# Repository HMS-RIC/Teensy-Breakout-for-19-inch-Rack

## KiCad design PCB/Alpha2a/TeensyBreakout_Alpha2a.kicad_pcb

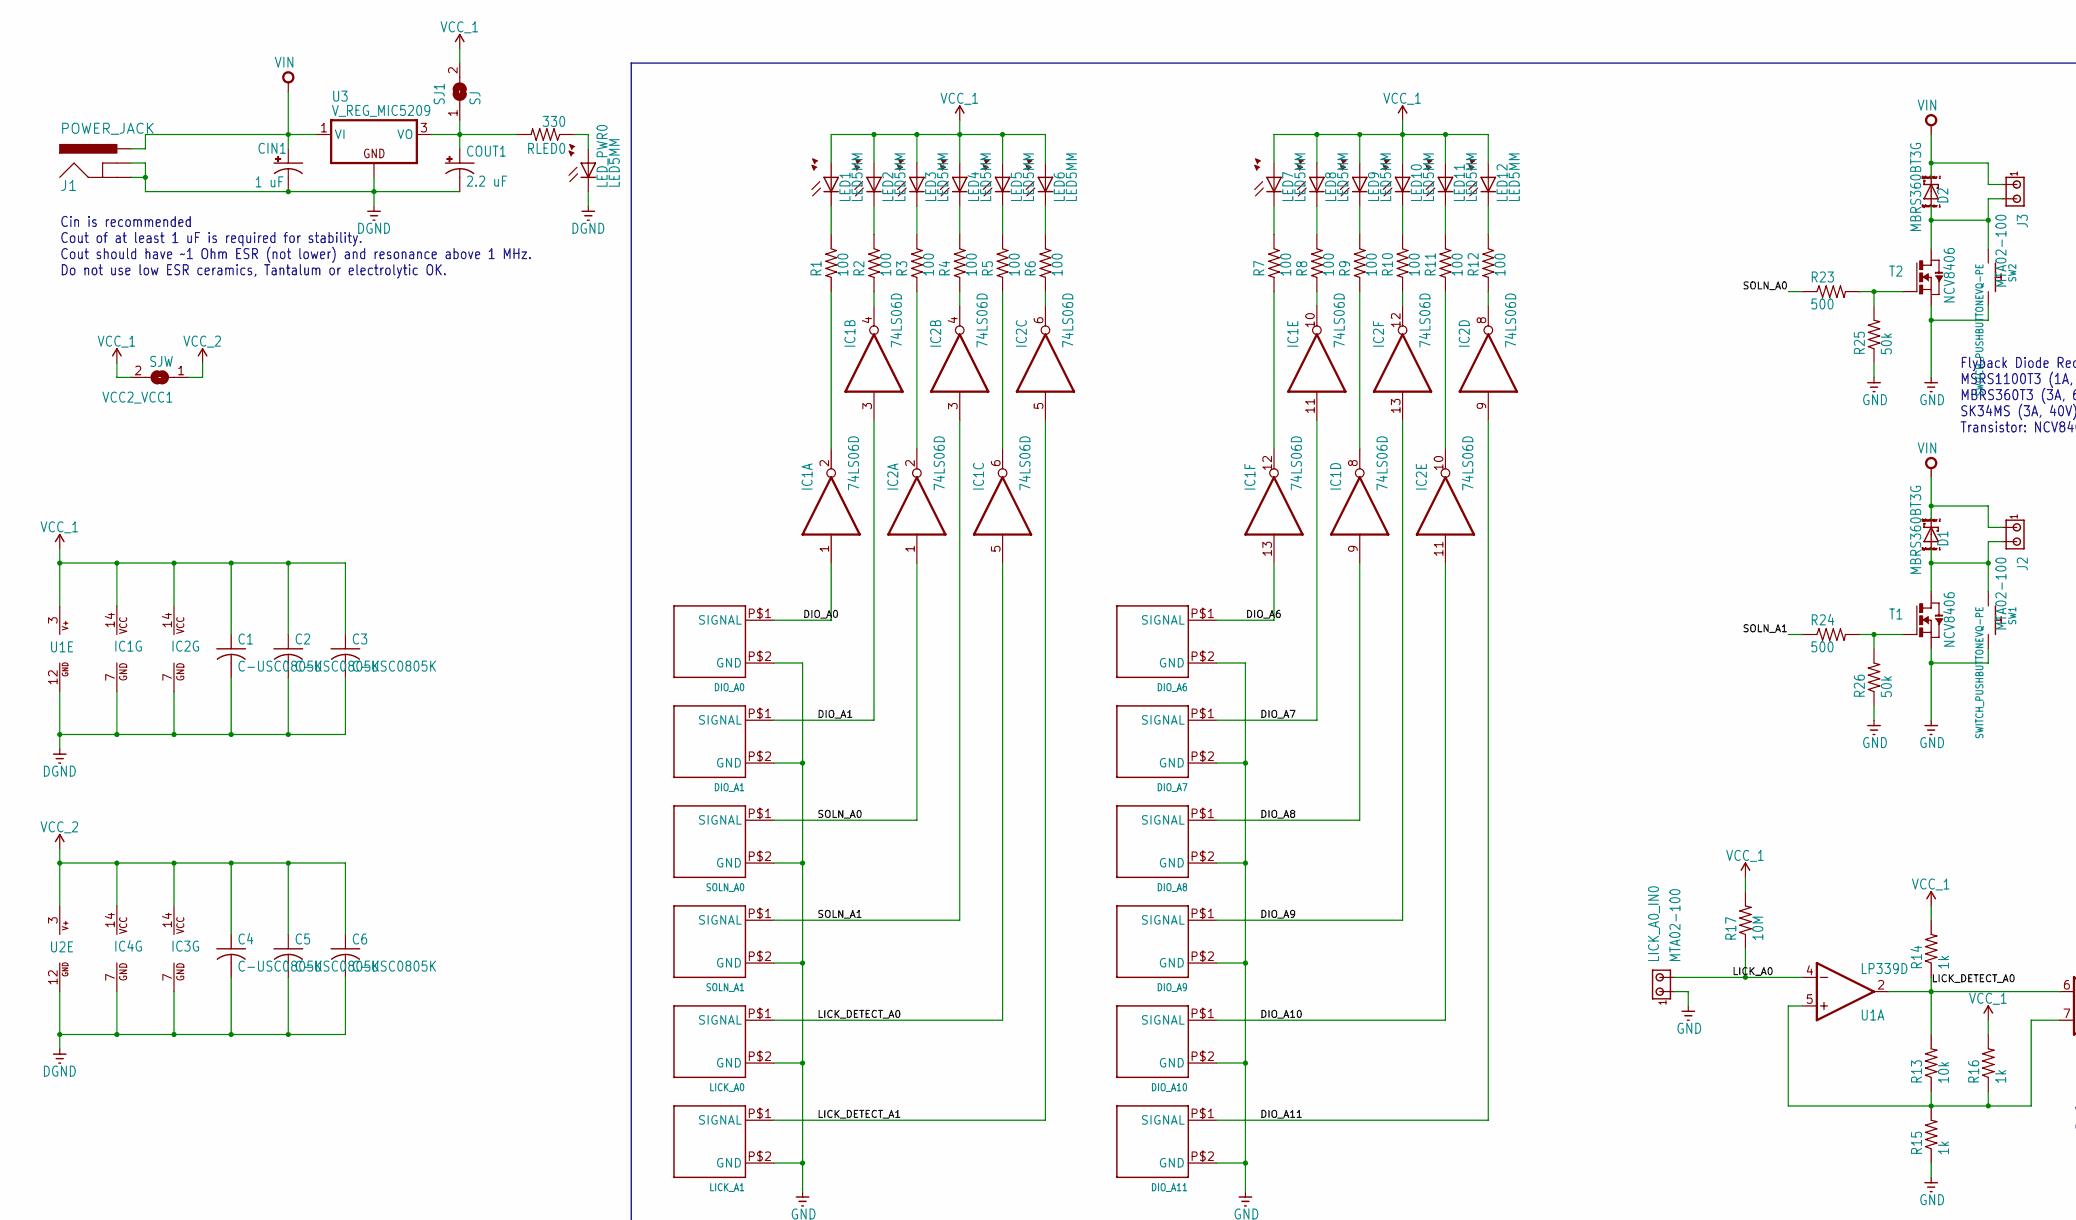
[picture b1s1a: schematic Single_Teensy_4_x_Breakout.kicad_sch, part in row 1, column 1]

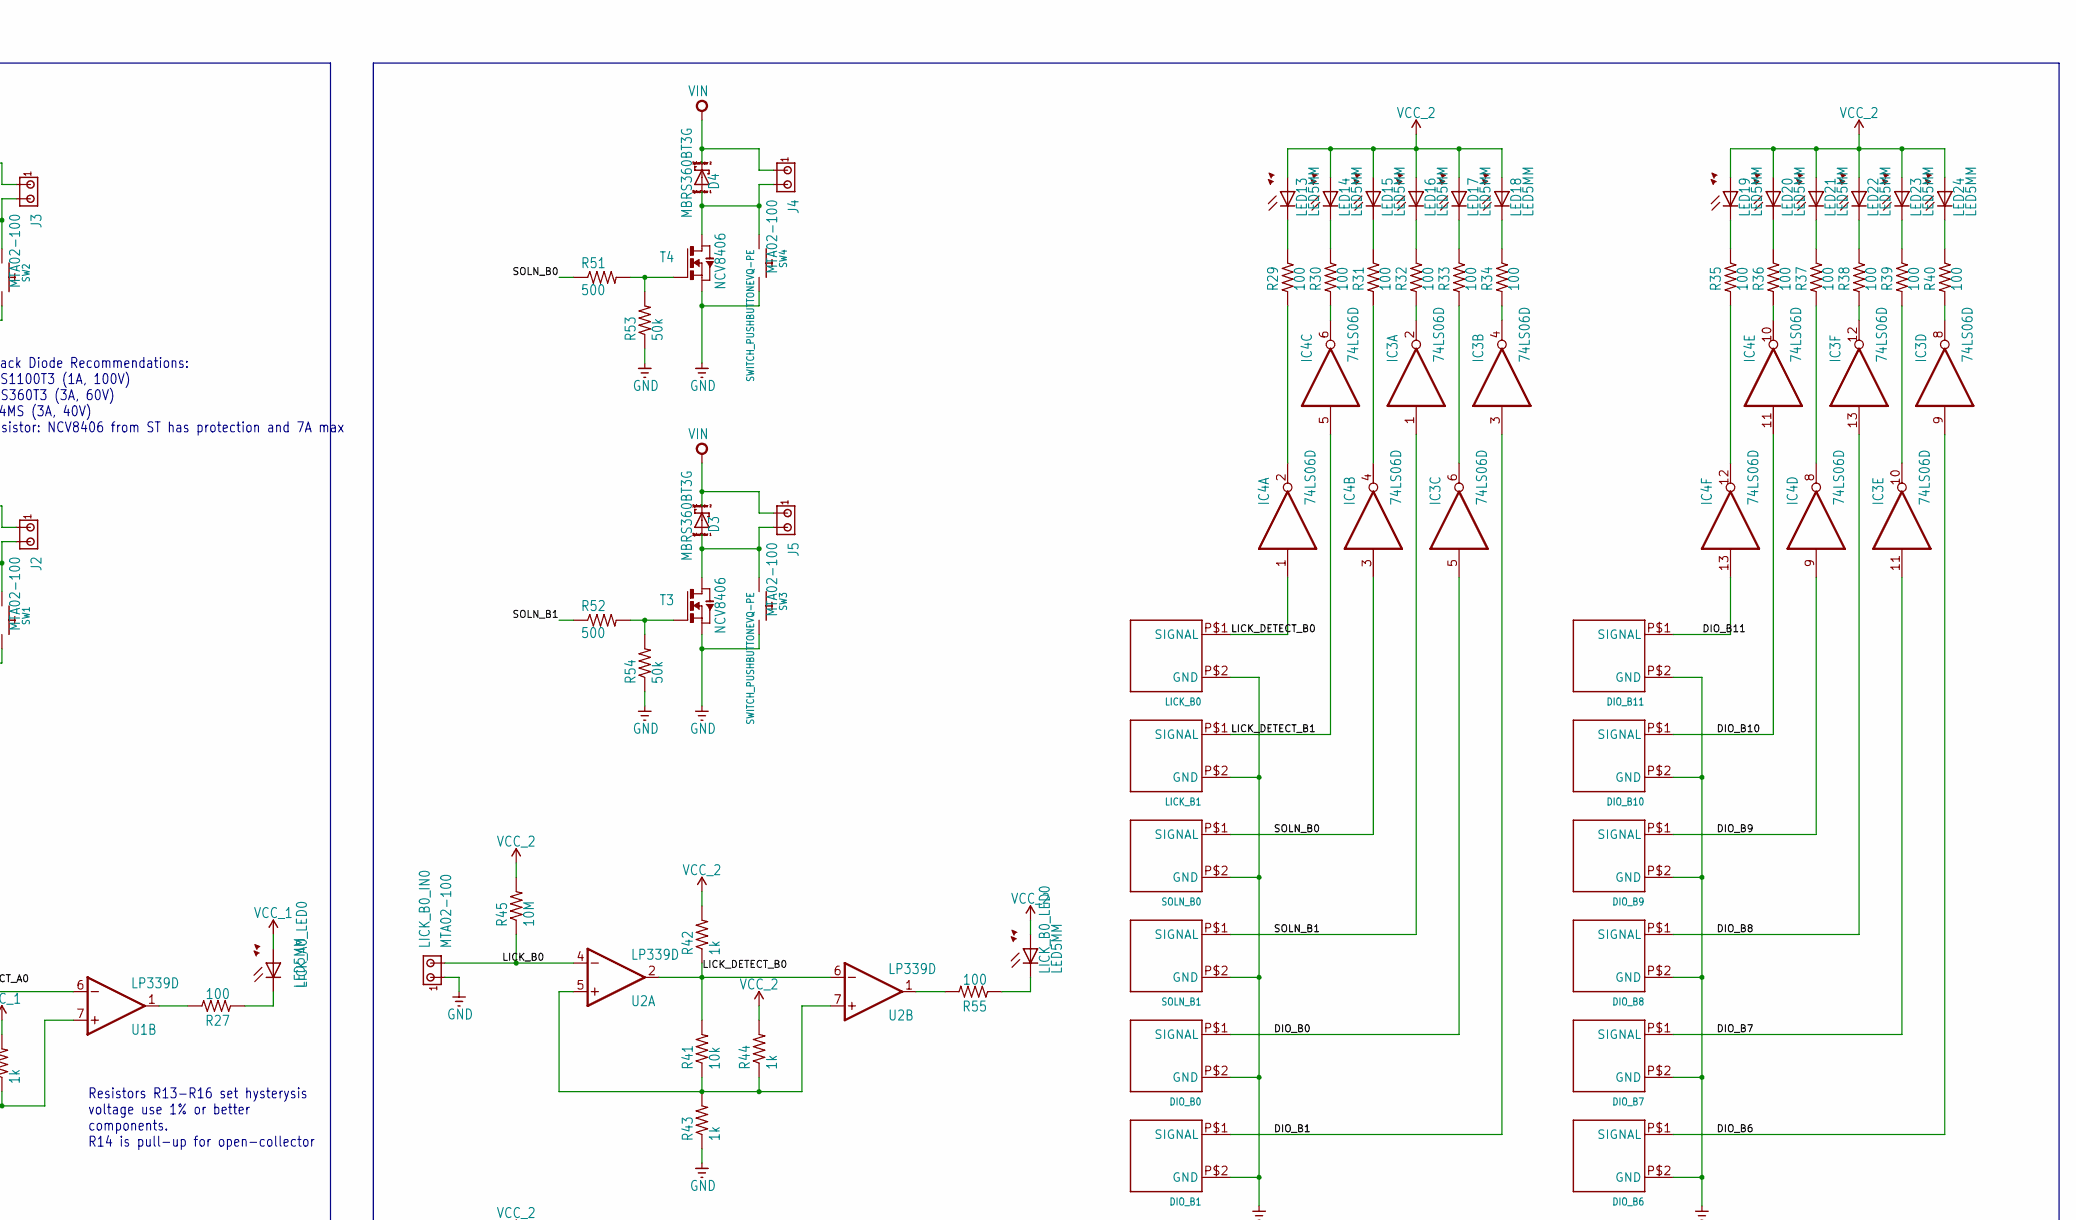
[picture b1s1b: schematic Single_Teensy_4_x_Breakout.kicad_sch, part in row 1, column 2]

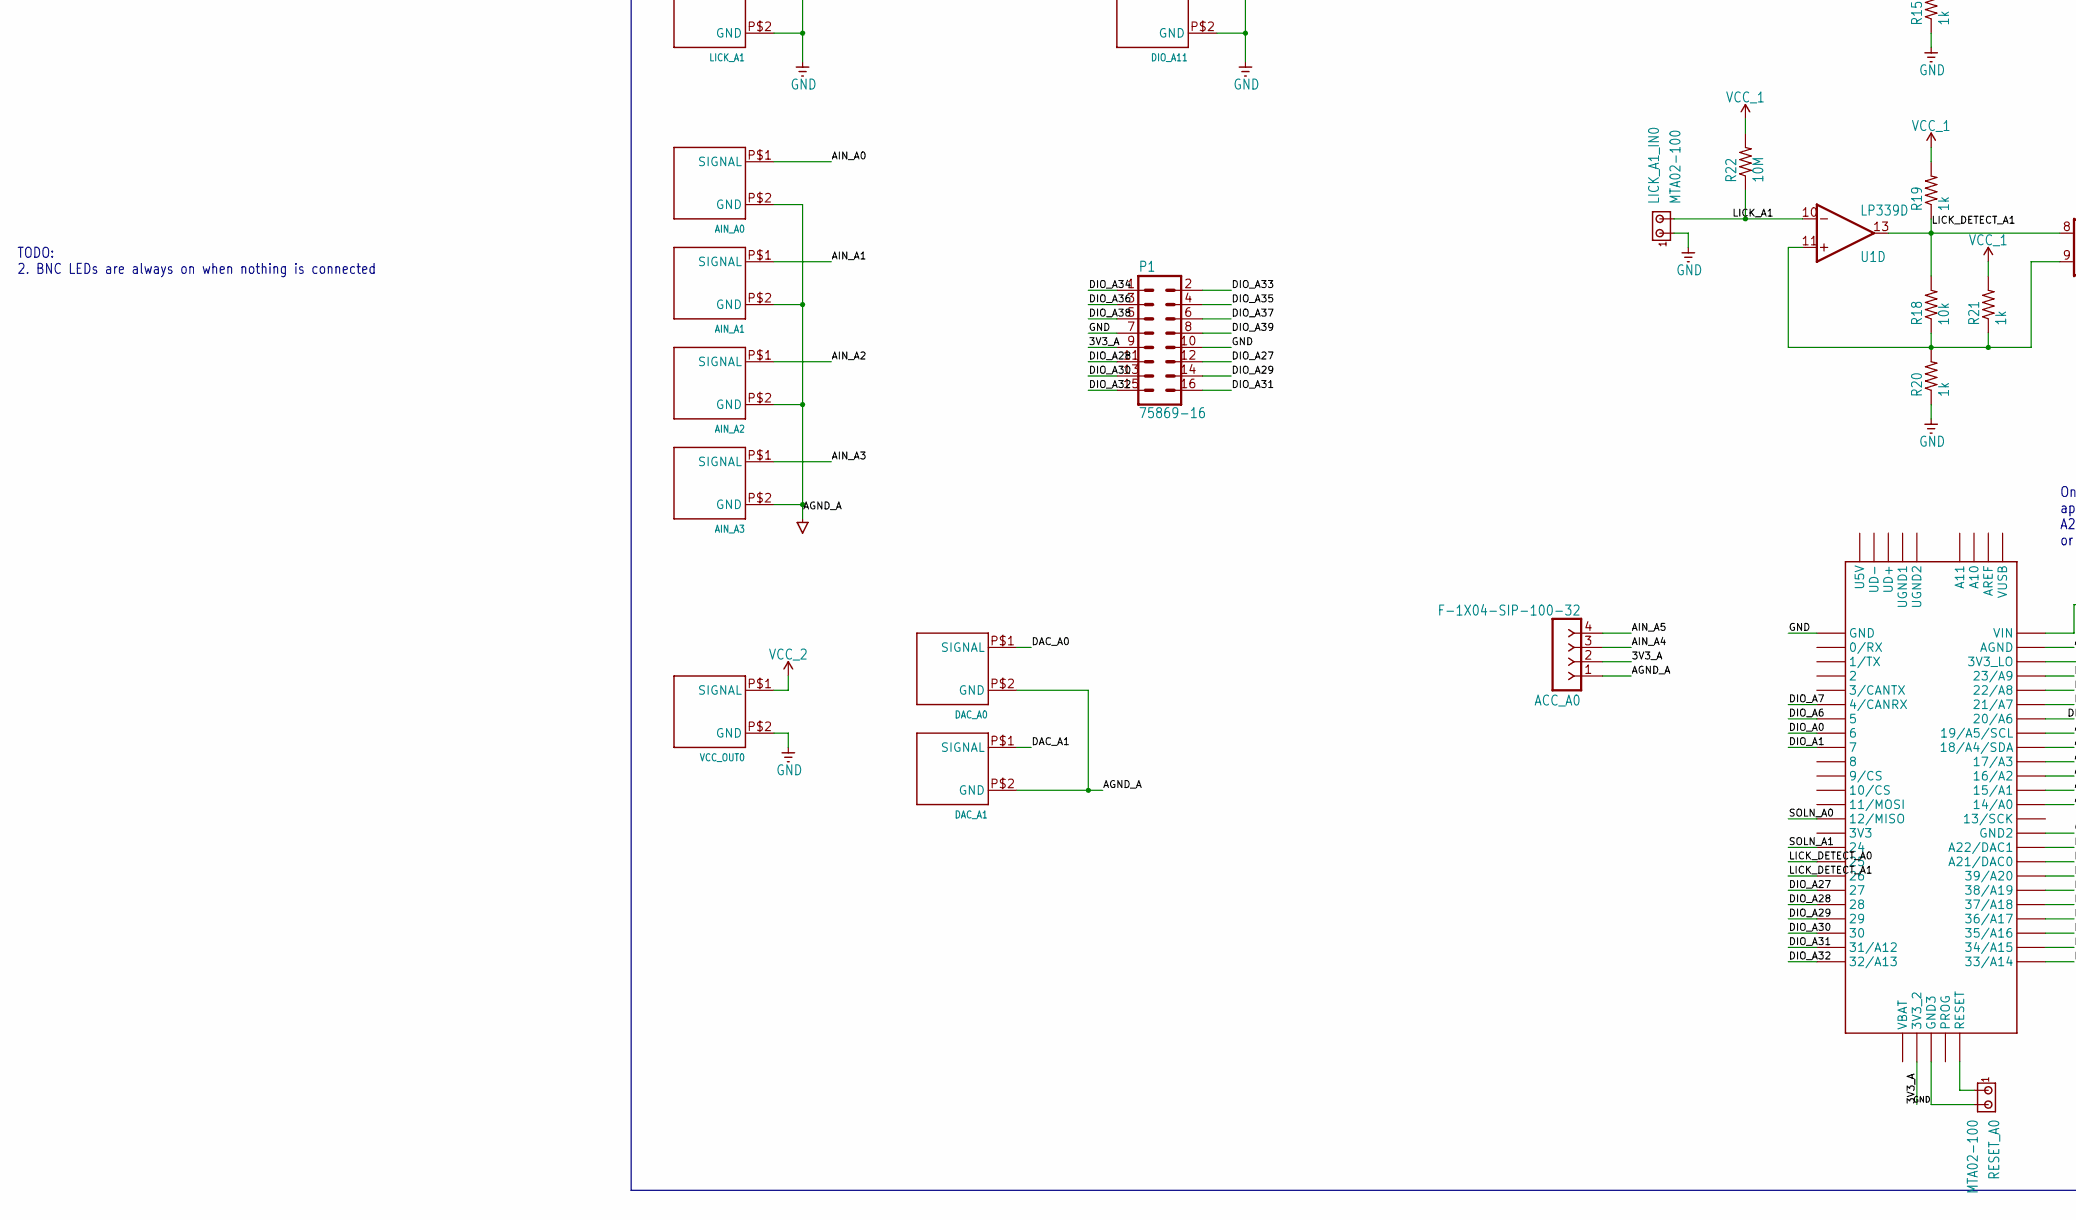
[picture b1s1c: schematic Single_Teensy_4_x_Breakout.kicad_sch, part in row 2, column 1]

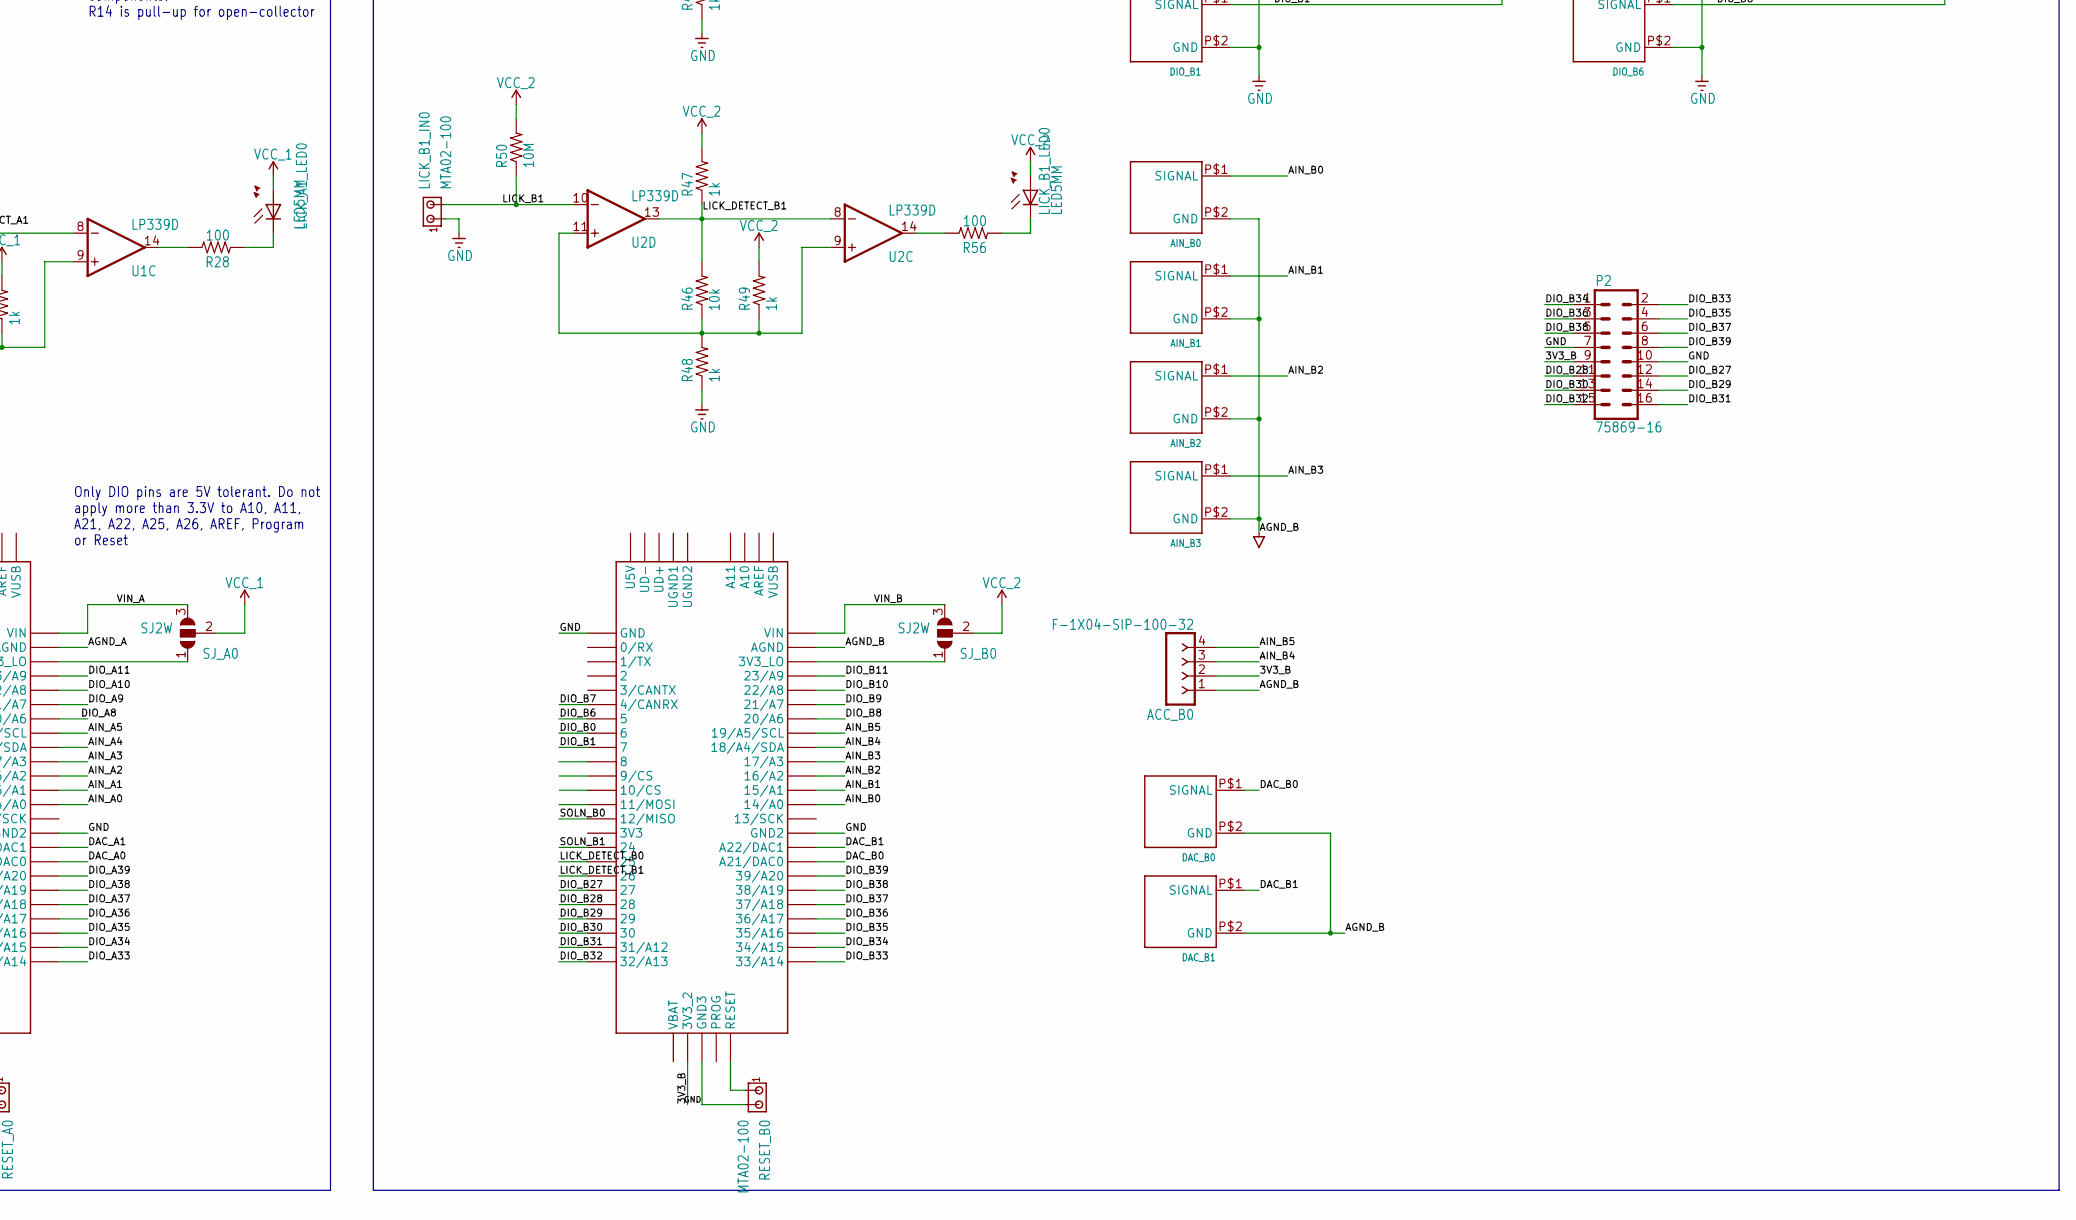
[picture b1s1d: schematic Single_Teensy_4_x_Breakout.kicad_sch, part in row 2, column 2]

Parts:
ACC_A0: F-1X04-SIP-100-32; SIP-100-04-32
ACC_B0: F-1X04-SIP-100-32; SIP-100-04-32
AIN_A0, AIN_A1, AIN_A2, AIN_A3: BNC_VERTICAL
AIN_B0, AIN_B1, AIN_B2, AIN_B3: BNC_VERTICAL
C1, C2, C3, C4, C5, C6: C-USC0805K; C0805K
CIN1: 1 uF; E2,5-5
COUT1: 2.2 uF; E2,5-5
D1, D2, D3, D4: MBRS360BT3G; DIODE_SMB
DAC_A0, DAC_A1: BNC_VERTICAL
DAC_B0, DAC_B1: BNC_VERTICAL
DIO_A0, DIO_A1, DIO_A6, DIO_A7, DIO_A8, DIO_A9, DIO_A10, DIO_A11: BNC_VERTICAL
DIO_B0, DIO_B1, DIO_B6, DIO_B7, DIO_B8, DIO_B9, DIO_B10, DIO_B11: BNC_VERTICAL
IC1, IC2, IC3, IC4: 74LS06D; SO14
J1: POWER_JACK; POWER_JACK_PTH
J2, J3, J4, J5: MTA02-100; 10X02MTA
LED1, LED2, LED3, LED4, LED5, LED6, LED7, LED8, LED9, LED10, LED11, LED12, LED13, LED14, LED15, LED16, LED17, LED18, LED19, LED20, LED21, LED22, LED23, LED24: LED5MM
LED_PWR0: LED5MM
LICK_A0, LICK_A1: BNC_VERTICAL
LICK_A0_IN0, LICK_A1_IN0: MTA02-100; 10X02MTA
LICK_A0_LED0, LICK_A1_LED0: LED5MM
LICK_B0, LICK_B1: BNC_VERTICAL
LICK_B0_IN0, LICK_B1_IN0: MTA02-100; 10X02MTA
LICK_B0_LED0, LICK_B1_LED0: LED5MM
P1, P2: 75869-16
R1, R2, R3, R4, R5, R6, R7, R8, R9, R10, R11, R12, R29, R30, R31, R32, R33, R34, R35, R36, R37, R38, R39, R40: 100; R1206MP
R13, R18, R41, R46: 10k; M0805
R14, R15, R16, R19, R20, R21, R42, R43, R44, R47, R48, R49: 1k; M0805
R17, R22, R45, R50: 10M; M0805
R23, R24, R51, R52: 500; M1206
R25, R26, R53, R54: 50k; M1206
R27, R28, R55, R56: 100; R1206
RESET_A0: MTA02-100; 10X02MTA
RESET_B0: MTA02-100; 10X02MTA
RLED0: 330; R0805
SJ1: SJ
SJ_A0: SJ2W; SJ_2
SJ_B0: SJ2W; SJ_2
SOLN_A0, SOLN_A1: BNC_VERTICAL
SOLN_B0, SOLN_B1: BNC_VERTICAL
SW1, SW2, SW3, SW4: SWITCH_PUSHBUTTONEVQ-PE; TACT_PANA-EVQ
T1, T2, T3, T4: NCV8406; SOT223
TEENSY_A0: TEENSY_3.5/3.6; TEENSY_3.5_3.6
TEENSY_B0: TEENSY_3.5/3.6; TEENSY_3.5_3.6
U1, U2: LP339D; SO14
U3: V_REG_MIC5209; SOT-223
VCC2_VCC1: SJW
VCC_OUT0: BNC_VERTICAL

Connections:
3V3_A: ACC_A0.2, P1.9, TEENSY_A0.3V3_2
3V3_B: ACC_B0.2, P2.9, TEENSY_B0.3V3_2
AIN_A0: AIN_A0.P$1 (SIGNAL), TEENSY_A0.14/A0
AIN_A1: AIN_A1.P$1 (SIGNAL), TEENSY_A0.15/A1
AIN_A2: AIN_A2.P$1 (SIGNAL), TEENSY_A0.16/A2
AIN_A3: AIN_A3.P$1 (SIGNAL), TEENSY_A0.17/A3
AIN_A4: ACC_A0.3, TEENSY_A0.18/A4/SDA
AIN_A5: ACC_A0.4, TEENSY_A0.19/A5/SCL
AIN_B0: AIN_B0.P$1 (SIGNAL), TEENSY_B0.14/A0
AIN_B1: AIN_B1.P$1 (SIGNAL), TEENSY_B0.15/A1
AIN_B2: AIN_B2.P$1 (SIGNAL), TEENSY_B0.16/A2
AIN_B3: AIN_B3.P$1 (SIGNAL), TEENSY_B0.17/A3
AIN_B4: ACC_B0.3, TEENSY_B0.18/A4/SDA
AIN_B5: ACC_B0.4, TEENSY_B0.19/A5/SCL
DAC_A0: DAC_A0.P$1 (SIGNAL), TEENSY_A0.21/DAC0 (A21/DAC0)
DAC_A1: DAC_A1.P$1 (SIGNAL), TEENSY_A0.A22/DAC1
DAC_B0: DAC_B0.P$1 (SIGNAL), TEENSY_B0.21/DAC0 (A21/DAC0)
DAC_B1: DAC_B1.P$1 (SIGNAL), TEENSY_B0.A22/DAC1
DIO_A0: DIO_A0.P$1 (SIGNAL), IC1.1 (I), TEENSY_A0.6
DIO_A1: DIO_A1.P$1 (SIGNAL), IC1.3 (I), TEENSY_A0.7
DIO_A6: DIO_A6.P$1 (SIGNAL), IC1.13 (I), TEENSY_A0.5
DIO_A7: DIO_A7.P$1 (SIGNAL), IC1.11 (I), TEENSY_A0.4/CANRX
DIO_A8: DIO_A8.P$1 (SIGNAL), IC1.9 (I), TEENSY_A0.20/A6
DIO_A9: DIO_A9.P$1 (SIGNAL), IC2.13 (I), TEENSY_A0.21/A7
DIO_A10: DIO_A10.P$1 (SIGNAL), IC2.11 (I), TEENSY_A0.22/A8
DIO_A11: DIO_A11.P$1 (SIGNAL), IC2.9 (I), TEENSY_A0.23/A9
DIO_A27: P1.12, TEENSY_A0.27
DIO_A28: P1.11, TEENSY_A0.28
DIO_A29: P1.14, TEENSY_A0.29
DIO_A30: P1.13, TEENSY_A0.30
DIO_A31: P1.16, TEENSY_A0.31/A12
DIO_A32: P1.15, TEENSY_A0.32/A13
DIO_A33: P1.2, TEENSY_A0.33/A14
DIO_A34: P1.1, TEENSY_A0.34/A15
DIO_A35: P1.4, TEENSY_A0.35/A16
DIO_A36: P1.3, TEENSY_A0.36/A17
DIO_A37: P1.6, TEENSY_A0.37/A18
DIO_A38: P1.5, TEENSY_A0.38/A19
DIO_A39: P1.8, TEENSY_A0.39/A20
DIO_B0: DIO_B0.P$1 (SIGNAL), IC3.5 (I), TEENSY_B0.6
DIO_B1: DIO_B1.P$1 (SIGNAL), IC3.3 (I), TEENSY_B0.7
DIO_B6: DIO_B6.P$1 (SIGNAL), IC3.9 (I), TEENSY_B0.5
DIO_B7: DIO_B7.P$1 (SIGNAL), IC3.11 (I), TEENSY_B0.4/CANRX
DIO_B8: DIO_B8.P$1 (SIGNAL), IC3.13 (I), TEENSY_B0.20/A6
DIO_B9: DIO_B9.P$1 (SIGNAL), IC4.9 (I), TEENSY_B0.21/A7
DIO_B10: DIO_B10.P$1 (SIGNAL), IC4.11 (I), TEENSY_B0.22/A8
DIO_B11: DIO_B11.P$1 (SIGNAL), IC4.13 (I), TEENSY_B0.23/A9
DIO_B27: P2.12, TEENSY_B0.27
DIO_B28: P2.11, TEENSY_B0.28
DIO_B29: P2.14, TEENSY_B0.29
DIO_B30: P2.13, TEENSY_B0.30
DIO_B31: P2.16, TEENSY_B0.31/A12
DIO_B32: P2.15, TEENSY_B0.32/A13
DIO_B33: P2.2, TEENSY_B0.33/A14
DIO_B34: P2.1, TEENSY_B0.34/A15
DIO_B35: P2.4, TEENSY_B0.35/A16
DIO_B36: P2.3, TEENSY_B0.36/A17
DIO_B37: P2.6, TEENSY_B0.37/A18
DIO_B38: P2.5, TEENSY_B0.38/A19
DIO_B39: P2.8, TEENSY_B0.39/A20
LICK_A0: LICK_A0_IN0.2, R17.1, U1.4 (-IN)
LICK_A1: LICK_A1_IN0.2, R22.1, U1.10 (-IN)
LICK_B0: LICK_B0_IN0.2, R45.1, U2.4 (-IN)
LICK_B1: LICK_B1_IN0.2, R50.1, U2.10 (-IN)
LICK_DETECT_A0: IC1.5 (I), LICK_A0.P$1 (SIGNAL), R13.2, R14.1, TEENSY_A0.25, U1.2 (OUT), U1.6 (-IN)
LICK_DETECT_A1: IC2.5 (I), LICK_A1.P$1 (SIGNAL), R18.2, R19.1, TEENSY_A0.26, U1.8 (-IN), U1.13 (OUT)
LICK_DETECT_B0: IC4.1 (I), LICK_B0.P$1 (SIGNAL), R41.2, R42.1, TEENSY_B0.25, U2.2 (OUT), U2.6 (-IN)
LICK_DETECT_B1: IC4.5 (I), LICK_B1.P$1 (SIGNAL), R46.2, R47.1, TEENSY_B0.26, U2.8 (-IN), U2.13 (OUT)
unnamed: IC1.2 (O), R1.1
unnamed: IC1.4 (O), R2.1
unnamed: IC2.4 (O), R4.1
unnamed: IC2.2 (O), R3.1
unnamed: IC1.6 (O), R5.1
unnamed: IC2.6 (O), R6.1
unnamed: LED1.K (C), R1.2
unnamed: LED2.K (C), R2.2
unnamed: LED3.K (C), R3.2
unnamed: LED4.K (C), R4.2
unnamed: LED5.K (C), R5.2
unnamed: LED6.K (C), R6.2
unnamed: R18.1, R20.2, R21.1, U1.9 (+IN), U1.11 (+IN)
unnamed: LED_PWR0.A, RLED0.1
unnamed: IC1.12 (O), R7.1
unnamed: IC1.10 (O), R8.1
unnamed: IC1.8 (O), R9.1
unnamed: IC2.12 (O), R10.1
unnamed: IC2.10 (O), R11.1
unnamed: IC2.8 (O), R12.1
unnamed: LED7.K (C), R7.2
unnamed: LED8.K (C), R8.2
unnamed: LED9.K (C), R9.2
unnamed: LED10.K (C), R10.2
unnamed: LED11.K (C), R11.2
unnamed: LED12.K (C), R12.2
unnamed: R13.1, R15.2, R16.1, U1.5 (+IN), U1.7 (+IN)
unnamed: SJ_A0.1, TEENSY_A0.3V3_LO
unnamed: COUT1.+, RLED0.2, SJ1.1, U3.3 (VO)
unnamed: R23.2, R25.2, T2.1 (G)
unnamed: R27.2, U1.1 (OUT)
unnamed: R24.2, R26.2, T1.1 (G)
unnamed: LICK_A0_LED0.K (C), R27.1
unnamed: IC4.4 (O), R31.1
unnamed: IC4.6 (O), R30.1
unnamed: IC3.6 (O), R33.1
unnamed: LICK_A1_LED0.K (C), R28.1
unnamed: IC3.4 (O), R34.1
unnamed: R28.2, U1.14 (OUT)
unnamed: SJ_B0.1, TEENSY_B0.3V3_LO
unnamed: IC3.2 (O), R32.1
unnamed: LED14.K (C), R30.2
unnamed: LED15.K (C), R31.2
unnamed: LED16.K (C), R32.2
unnamed: LED17.K (C), R33.2
unnamed: LED18.K (C), R34.2
unnamed: IC4.12 (O), R35.1
unnamed: IC4.10 (O), R36.1
unnamed: IC4.8 (O), R37.1
unnamed: IC3.12 (O), R38.1
unnamed: IC3.10 (O), R39.1
unnamed: IC3.8 (O), R40.1
unnamed: LED19.K (C), R35.2
unnamed: LED20.K (C), R36.2
unnamed: LED21.K (C), R37.2
unnamed: LED22.K (C), R38.2
unnamed: LED23.K (C), R39.2
unnamed: LED24.K (C), R40.2
unnamed: R51.2, R53.2, T4.1 (G)
unnamed: R52.2, R54.2, T3.1 (G)
unnamed: IC4.2 (O), R29.1
unnamed: LED13.K (C), R29.2
unnamed: R41.1, R43.2, R44.1, U2.5 (+IN), U2.7 (+IN)
unnamed: R46.1, R48.2, R49.1, U2.9 (+IN), U2.11 (+IN)
unnamed: R55.2, U2.1 (OUT)
unnamed: LICK_B0_LED0.K (C), R55.1
unnamed: LICK_B1_LED0.K (C), R56.1
unnamed: R56.2, U2.14 (OUT)
RESET_A: RESET_A0.1, TEENSY_A0.RESET
RESET_B: RESET_B0.1, TEENSY_B0.RESET
SOLN_A0: IC2.1 (I), R23.1, SOLN_A0.P$1 (SIGNAL), TEENSY_A0.12/MISO
SOLN_A1: IC2.3 (I), R24.1, SOLN_A1.P$1 (SIGNAL), TEENSY_A0.24
SOLN_B0: IC4.3 (I), R51.1, SOLN_B0.P$1 (SIGNAL), TEENSY_B0.12/MISO
SOLN_B1: IC3.1 (I), R52.1, SOLN_B1.P$1 (SIGNAL), TEENSY_B0.24
VCC_1: C1.1, C2.1, C3.1, IC1.14 (VCC), IC2.14 (VCC), LED1.A, LED2.A, LED3.A, LED4.A, LED5.A, LED6.A, LED7.A, LED8.A, LED9.A, LED10.A, LED11.A, LED12.A, LICK_A0_LED0.A, LICK_A1_LED0.A, R14.2, R16.2, R17.2, R19.2, R21.2, R22.2, SJ1.2, SJ_A0.2, U1.3 (V+), VCC2_VCC1.2
VCC_2: C4.1, C5.1, C6.1, IC3.14 (VCC), IC4.14 (VCC), LED13.A, LED14.A, LED15.A, LED16.A, LED17.A, LED18.A, LED19.A, LED20.A, LED21.A, LED22.A, LED23.A, LED24.A, LICK_B0_LED0.A, LICK_B1_LED0.A, R42.2, R44.2, R45.2, R47.2, R49.2, R50.2, SJ_B0.2, U2.3 (V+), VCC2_VCC1.1, VCC_OUT0.P$1 (SIGNAL)
VIN: CIN1.+, D1.C (A), D2.C (A), D3.C (A), D4.C (A), J1.PWR, J2.1, J3.1, J4.1, J5.1, U3.1 (VI)
VIN_A: SJ_A0.3, TEENSY_A0.VIN
VIN_B: SJ_B0.3, TEENSY_B0.VIN
VOUT-2: D1.A (C), J2.2, SW1.P$1, T1.2 (D), T1.4 (D)
VOUT-3: D2.A (C), J3.2, SW2.P$1, T2.2 (D), T2.4 (D)
VOUT-5: D4.A (C), J4.2, SW4.P$1, T4.2 (D), T4.4 (D)
VOUT-6: D3.A (C), J5.2, SW3.P$1, T3.2 (D), T3.4 (D)

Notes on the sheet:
Flyback Diode Recommendations: MSRS1100T3 (1A, 100V) MBRS360T3 (3A, 60V) SK34MS (3A, 40V) Transistor: NCV8406 from ST has protection and 7A max
Resistors R13-R16 set hysterysis voltage use 1% or better components. R14 is pull-up for open-collector
Cin is recommended Cout of at least 1 uF is required for stability. Cout should have ~1 Ohm ESR (not lower) and resonance above 1 MHz. Do not use low ESR ceramics, Tantalum or electrolytic OK.
Only DIO pins are 5V tolerant. Do not apply more than 3.3V to A10, A11, A21, A22, A25, A26, AREF, Program or Reset
TODO: 2. BNC LEDs are always on when nothing is connected~{}

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
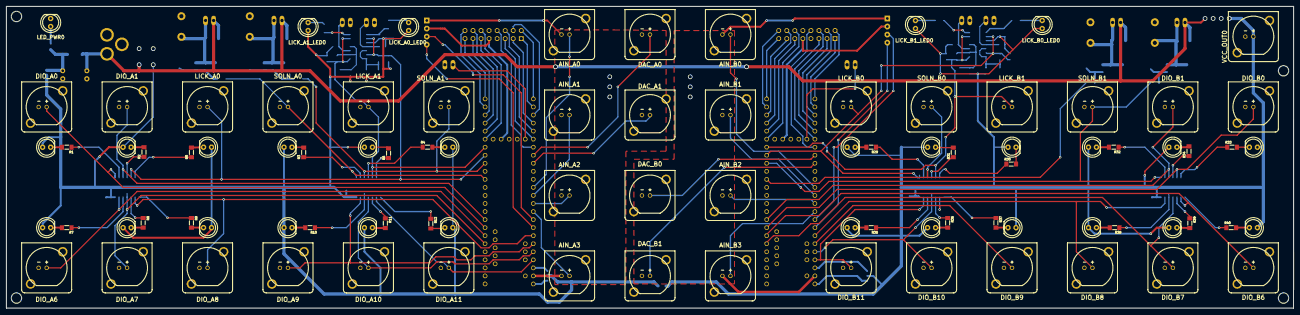
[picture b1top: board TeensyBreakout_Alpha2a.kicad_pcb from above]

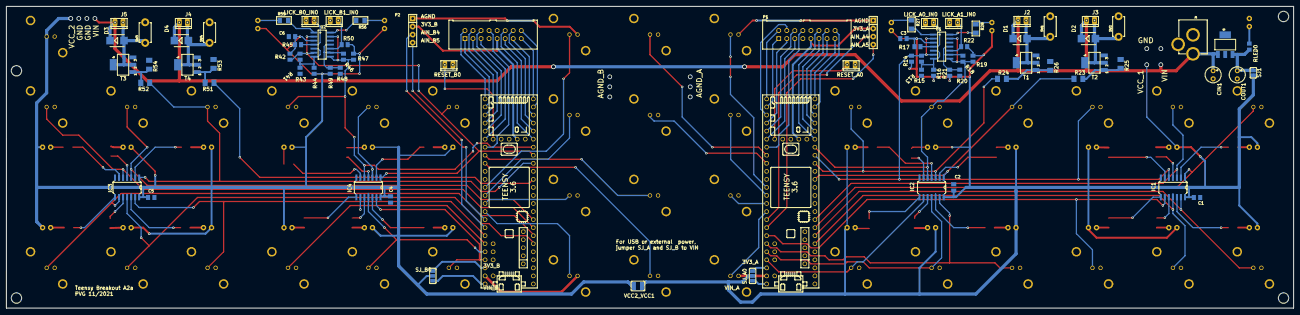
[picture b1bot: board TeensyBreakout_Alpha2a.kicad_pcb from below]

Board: 2 copper layers, 406.4 x 95.2 mm, 175 parts (81 on the bottom side), 154 nets.

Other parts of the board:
UNK_HOLE_0: dummyfp0
UNK_HOLE_1: dummyfp1
UNK_HOLE_2: dummyfp2
UNK_HOLE_3: dummyfp3
